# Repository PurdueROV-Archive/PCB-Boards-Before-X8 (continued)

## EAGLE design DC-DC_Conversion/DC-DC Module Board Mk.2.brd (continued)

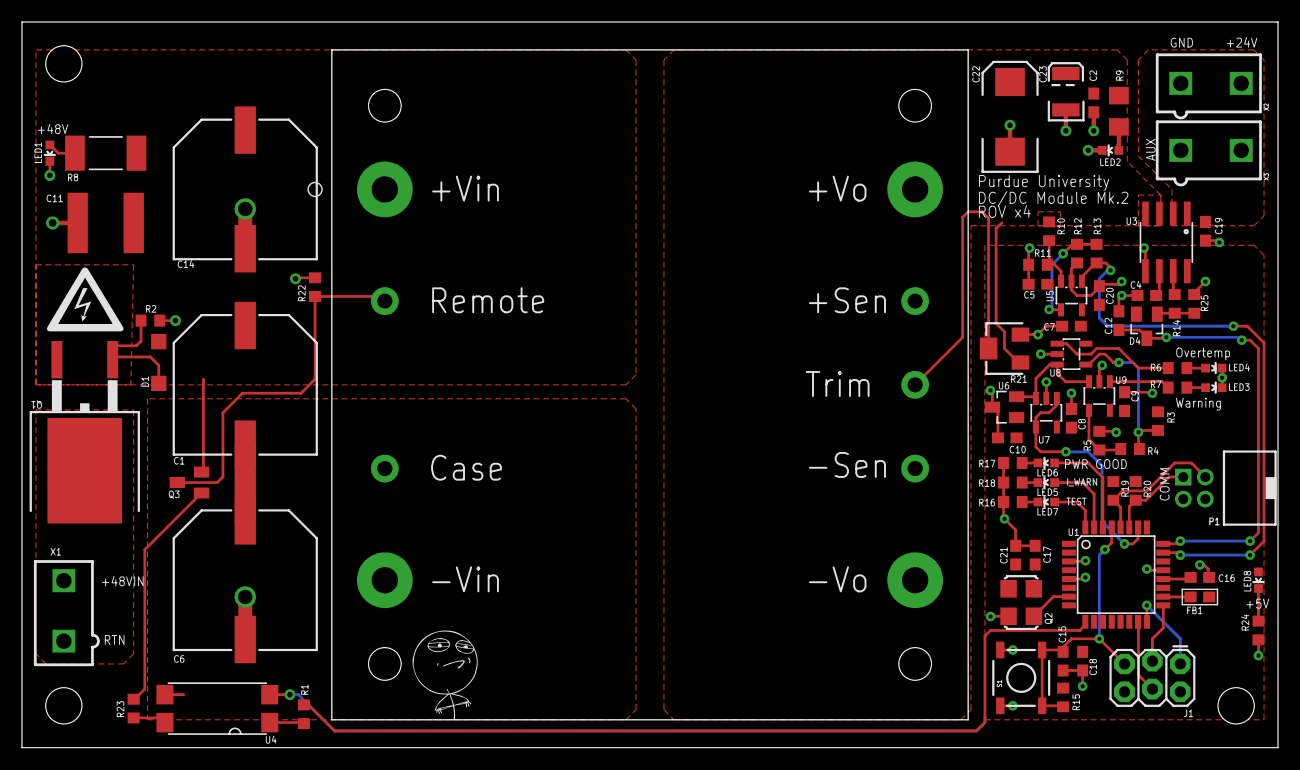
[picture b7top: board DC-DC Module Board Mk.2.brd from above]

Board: 2 copper layers, 114.3 x 66.0 mm, 78 parts (0 on the bottom side), 48 nets.

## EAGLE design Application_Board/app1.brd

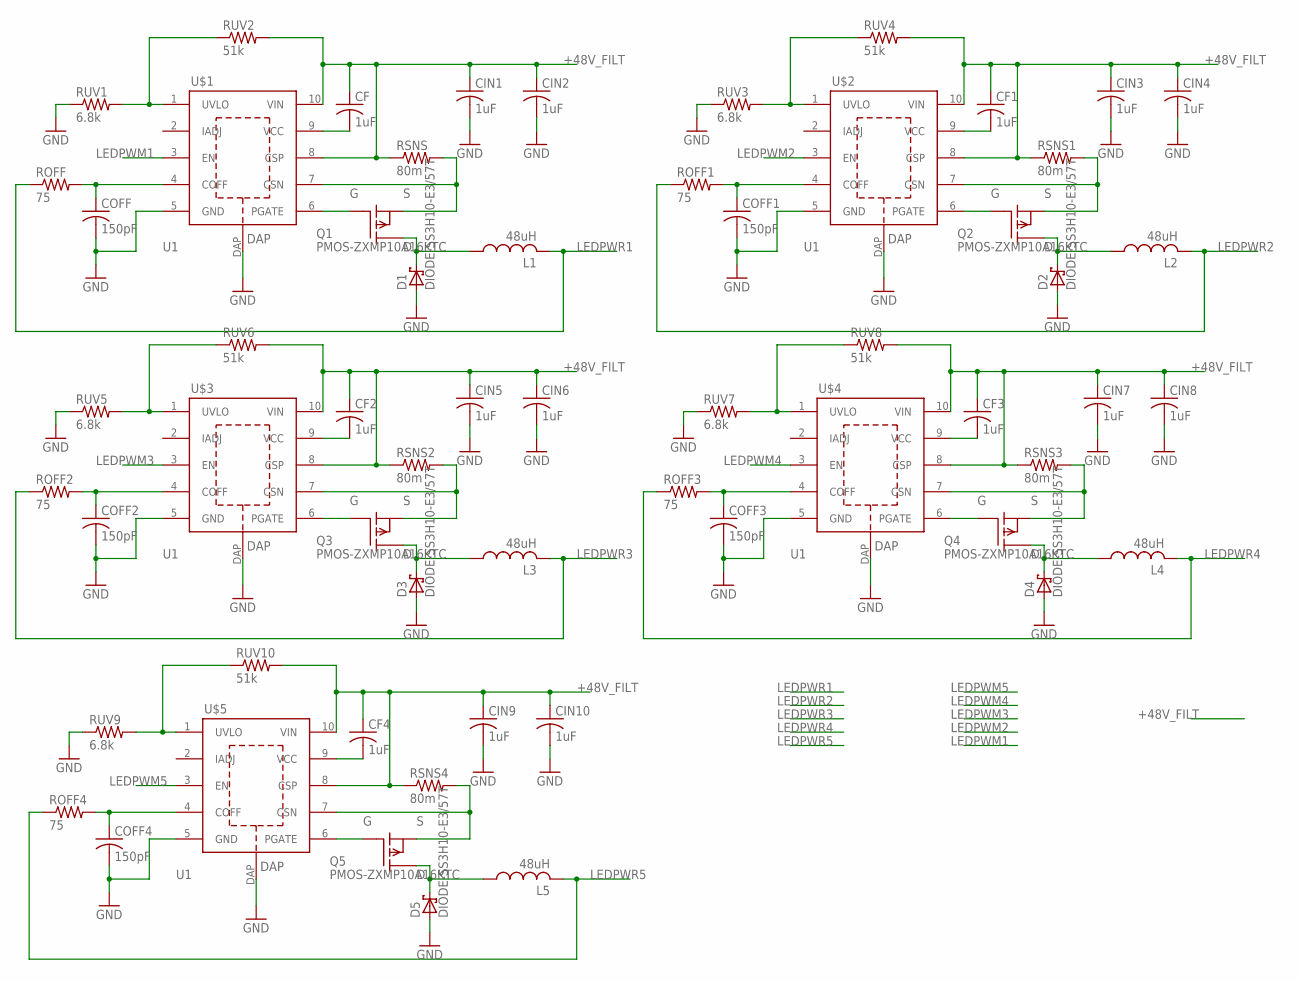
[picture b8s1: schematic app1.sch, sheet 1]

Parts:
CF, CF1, CF2, CF3, CF4: 1uF; C0603
CIN1, CIN2, CIN3, CIN4, CIN5, CIN6, CIN7, CIN8, CIN9, CIN10: 1uF; C1206
COFF, COFF1, COFF2, COFF3, COFF4: 150pF; C0603
D1, D2, D3, D4, D5: DIODE-SS3H10-E3/57T; SMC
L1, L2, L3, L4, L5: 48uH; SRP1265A
Q1, Q2, Q3, Q4, Q5: PMOS-ZXMP10A16KTC; TO252
ROFF, ROFF1, ROFF2, ROFF3, ROFF4: 75; R0603
RSNS, RSNS1, RSNS2, RSNS3, RSNS4: 80m; R2512
RUV1, RUV3, RUV5, RUV7, RUV9: 6.8k; R0603
RUV2, RUV4, RUV6, RUV8, RUV10: 51k; R0603
U$1, U$2, U$3, U$4, U$5: U1; VSSOP-10

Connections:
+48V_FILT: CF.1, CF1.1, CF2.1, CF3.1, CF4.1, CIN1.1, CIN2.1, CIN3.1, CIN4.1, CIN5.1, CIN6.1, CIN7.1, CIN8.1, CIN9.1, CIN10.1, RSNS.1, RSNS1.1, RSNS2.1, RSNS3.1, RSNS4.1, RUV2.2, RUV4.2, RUV6.2, RUV8.2, RUV10.2, U$1.8 (CSP), U$1.10 (VIN), U$2.8 (CSP), U$2.10 (VIN), U$3.8 (CSP), U$3.10 (VIN), U$4.8 (CSP), U$4.10 (VIN), U$5.8 (CSP), U$5.10 (VIN); also elsewhere on the board
GND: CIN1.2, CIN2.2, CIN3.2, CIN4.2, CIN5.2, CIN6.2, CIN7.2, CIN8.2, CIN9.2, CIN10.2, COFF.2, COFF1.2, COFF2.2, COFF3.2, COFF4.2, D1.A, D2.A, D3.A, D4.A, D5.A, RUV1.1, RUV3.1, RUV5.1, RUV7.1, RUV9.1, U$1.5 (GND), U$1.DAP, U$2.5 (GND), U$2.DAP, U$3.5 (GND), U$3.DAP, U$4.5 (GND), U$4.DAP, U$5.5 (GND), U$5.DAP; also elsewhere on the board
LEDPWM1: U$1.3 (EN); also elsewhere on the board
LEDPWM2: U$2.3 (EN); also elsewhere on the board
LEDPWM3: U$3.3 (EN); also elsewhere on the board
LEDPWM4: U$4.3 (EN); also elsewhere on the board
LEDPWM5: U$5.3 (EN); also elsewhere on the board
LEDPWR1: L1.P$2 (2), ROFF.1; also elsewhere on the board
LEDPWR2: L2.P$2 (2), ROFF1.1; also elsewhere on the board
LEDPWR3: L3.P$2 (2), ROFF2.1; also elsewhere on the board
LEDPWR4: L4.P$2 (2), ROFF3.1; also elsewhere on the board
LEDPWR5: L5.P$2 (2), ROFF4.1; also elsewhere on the board
unnamed: RUV3.2, RUV4.1, U$2.1 (UVLO)
unnamed: RUV1.2, RUV2.1, U$1.1 (UVLO)
unnamed: CF.2, U$1.9 (VCC)
unnamed: Q1.2 (S), RSNS.2, U$1.7 (CSN)
unnamed: COFF.1, ROFF.2, U$1.4 (COFF)
unnamed: Q1.1 (G), U$1.6 (PGATE)
unnamed: D1.C, L1.P$1 (1), Q1.3 (D)
unnamed: CF1.2, U$2.9 (VCC)
unnamed: Q2.2 (S), RSNS1.2, U$2.7 (CSN)
unnamed: COFF1.1, ROFF1.2, U$2.4 (COFF)
unnamed: Q2.1 (G), U$2.6 (PGATE)
unnamed: D2.C, L2.P$1 (1), Q2.3 (D)
unnamed: RUV5.2, RUV6.1, U$3.1 (UVLO)
unnamed: CF2.2, U$3.9 (VCC)
unnamed: Q3.2 (S), RSNS2.2, U$3.7 (CSN)
unnamed: COFF2.1, ROFF2.2, U$3.4 (COFF)
unnamed: Q3.1 (G), U$3.6 (PGATE)
unnamed: D3.C, L3.P$1 (1), Q3.3 (D)
unnamed: RUV7.2, RUV8.1, U$4.1 (UVLO)
unnamed: CF3.2, U$4.9 (VCC)
unnamed: Q4.2 (S), RSNS3.2, U$4.7 (CSN)
unnamed: COFF3.1, ROFF3.2, U$4.4 (COFF)
unnamed: Q4.1 (G), U$4.6 (PGATE)
unnamed: D4.C, L4.P$1 (1), Q4.3 (D)
unnamed: RUV9.2, RUV10.1, U$5.1 (UVLO)
unnamed: CF4.2, U$5.9 (VCC)
unnamed: Q5.2 (S), RSNS4.2, U$5.7 (CSN)
unnamed: COFF4.1, ROFF4.2, U$5.4 (COFF)
unnamed: Q5.1 (G), U$5.6 (PGATE)
unnamed: D5.C, L5.P$1 (1), Q5.3 (D)

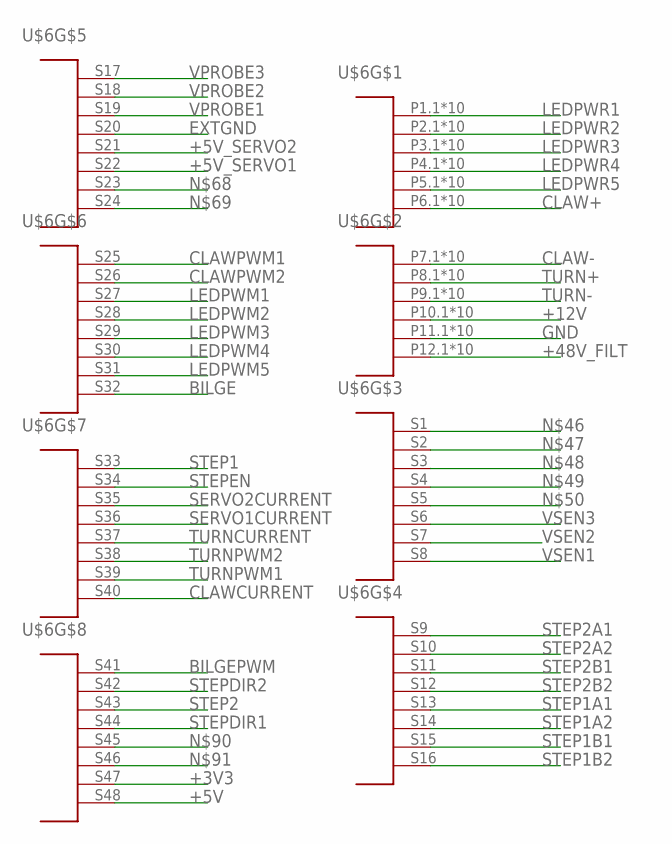
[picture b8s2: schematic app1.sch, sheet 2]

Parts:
U$6: TEN60-P6-S24-S24-P6-RA

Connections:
+3V3: U$6.S47; also elsewhere on the board
+5V: U$6.S48; also elsewhere on the board
+5V_SERVO1: U$6.S22; also elsewhere on the board
+5V_SERVO2: U$6.S21; also elsewhere on the board
+12V: U$6.P10.1, U$6.P10.2, U$6.P10.3, U$6.P10.4, U$6.P10.5, U$6.P10.6, U$6.P10.7, U$6.P10.8, U$6.P10.9, U$6.P10.10; also elsewhere on the board
+48V_FILT: U$6.P12.1, U$6.P12.2, U$6.P12.3, U$6.P12.4, U$6.P12.5, U$6.P12.6, U$6.P12.7, U$6.P12.8, U$6.P12.9, U$6.P12.10; also elsewhere on the board
BILGE: U$6.S32; also elsewhere on the board
BILGEPWM: U$6.S41; also elsewhere on the board
CLAW+: U$6.P6.1, U$6.P6.2, U$6.P6.3, U$6.P6.4, U$6.P6.5, U$6.P6.6, U$6.P6.7, U$6.P6.8, U$6.P6.9, U$6.P6.10; also elsewhere on the board
CLAW-: U$6.P7.1, U$6.P7.2, U$6.P7.3, U$6.P7.4, U$6.P7.5, U$6.P7.6, U$6.P7.7, U$6.P7.8, U$6.P7.9, U$6.P7.10; also elsewhere on the board
CLAWCURRENT: U$6.S40; also elsewhere on the board
CLAWPWM1: U$6.S25; also elsewhere on the board
CLAWPWM2: U$6.S26; also elsewhere on the board
EXTGND: U$6.S20; also elsewhere on the board
GND: U$6.P11.1, U$6.P11.2, U$6.P11.3, U$6.P11.4, U$6.P11.5, U$6.P11.6, U$6.P11.7, U$6.P11.8, U$6.P11.9, U$6.P11.10; also elsewhere on the board
LEDPWM1: U$6.S27; also elsewhere on the board
LEDPWM2: U$6.S28; also elsewhere on the board
LEDPWM3: U$6.S29; also elsewhere on the board
LEDPWM4: U$6.S30; also elsewhere on the board
LEDPWM5: U$6.S31; also elsewhere on the board
LEDPWR1: U$6.P1.1, U$6.P1.2, U$6.P1.3, U$6.P1.4, U$6.P1.5, U$6.P1.6, U$6.P1.7, U$6.P1.8, U$6.P1.9, U$6.P1.10; also elsewhere on the board
LEDPWR2: U$6.P2.1, U$6.P2.2, U$6.P2.3, U$6.P2.4, U$6.P2.5, U$6.P2.6, U$6.P2.7, U$6.P2.8, U$6.P2.9, U$6.P2.10; also elsewhere on the board
LEDPWR3: U$6.P3.1, U$6.P3.2, U$6.P3.3, U$6.P3.4, U$6.P3.5, U$6.P3.6, U$6.P3.7, U$6.P3.8, U$6.P3.9, U$6.P3.10; also elsewhere on the board
LEDPWR4: U$6.P4.1, U$6.P4.2, U$6.P4.3, U$6.P4.4, U$6.P4.5, U$6.P4.6, U$6.P4.7, U$6.P4.8, U$6.P4.9, U$6.P4.10; also elsewhere on the board
LEDPWR5: U$6.P5.1, U$6.P5.2, U$6.P5.3, U$6.P5.4, U$6.P5.5, U$6.P5.6, U$6.P5.7, U$6.P5.8, U$6.P5.9, U$6.P5.10; also elsewhere on the board
SERVO1CURRENT: U$6.S36; also elsewhere on the board
SERVO2CURRENT: U$6.S35; also elsewhere on the board
STEP1: U$6.S33; also elsewhere on the board
STEP1A1: U$6.S13; also elsewhere on the board
STEP1A2: U$6.S14; also elsewhere on the board
STEP1B1: U$6.S15; also elsewhere on the board
STEP1B2: U$6.S16; also elsewhere on the board
STEP2: U$6.S43; also elsewhere on the board
STEP2A1: U$6.S9; also elsewhere on the board
STEP2A2: U$6.S10; also elsewhere on the board
STEP2B1: U$6.S11; also elsewhere on the board
STEP2B2: U$6.S12; also elsewhere on the board
STEPDIR1: U$6.S44; also elsewhere on the board
STEPDIR2: U$6.S42; also elsewhere on the board
STEPEN: U$6.S34; also elsewhere on the board
TURN+: U$6.P8.1, U$6.P8.2, U$6.P8.3, U$6.P8.4, U$6.P8.5, U$6.P8.6, U$6.P8.7, U$6.P8.8, U$6.P8.9, U$6.P8.10; also elsewhere on the board
TURN-: U$6.P9.1, U$6.P9.2, U$6.P9.3, U$6.P9.4, U$6.P9.5, U$6.P9.6, U$6.P9.7, U$6.P9.8, U$6.P9.9, U$6.P9.10; also elsewhere on the board
TURNCURRENT: U$6.S37; also elsewhere on the board
TURNPWM1: U$6.S39; also elsewhere on the board
TURNPWM2: U$6.S38; also elsewhere on the board
VPROBE1: U$6.S19; also elsewhere on the board
VPROBE2: U$6.S18; also elsewhere on the board
VPROBE3: U$6.S17; also elsewhere on the board
VSEN1: U$6.S8; also elsewhere on the board
VSEN2: U$6.S7; also elsewhere on the board
VSEN3: U$6.S6; also elsewhere on the board

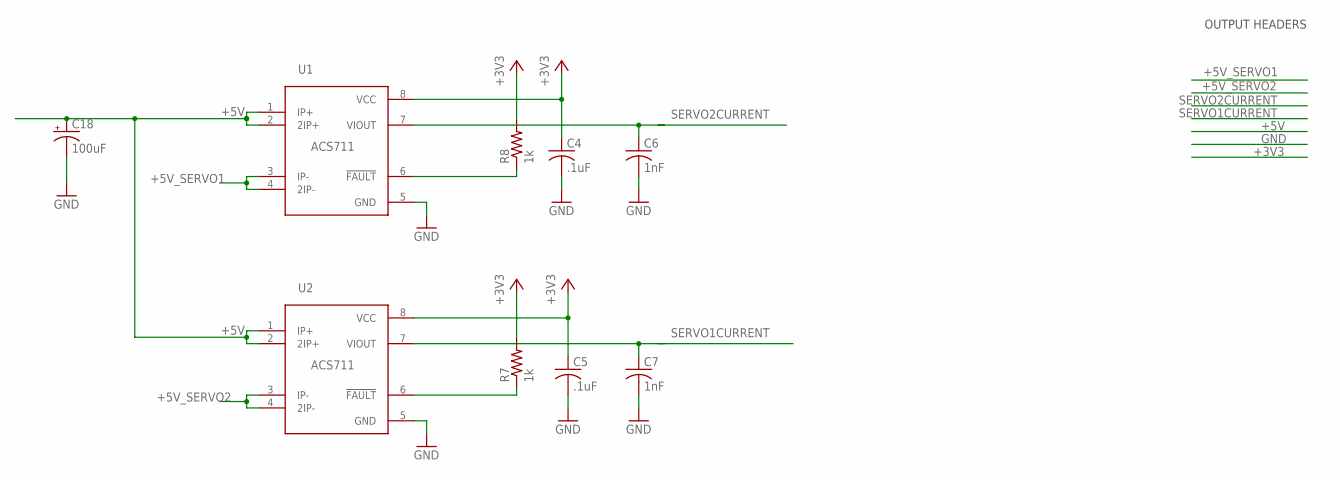
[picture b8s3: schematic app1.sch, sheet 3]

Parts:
C4, C5: .1uF; C0603
C6, C7: 1nF; C0603K
C18: 100uF; SANYO-OSCON_SMD_B6
R7, R8: 1k; R0603
U1, U2: ACS711; 8SOIC

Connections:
+3V3: C4.1, C5.1, R7.2, R8.2, U1.8 (VCC), U2.8 (VCC); also elsewhere on the board
+5V: C18.+, U1.1 (IP+), U1.2 (2IP+), U2.1 (IP+), U2.2 (2IP+); also elsewhere on the board
+5V_SERVO1: U1.3 (IP-), U1.4 (2IP-); also elsewhere on the board
+5V_SERVO2: U2.3 (IP-), U2.4 (2IP-); also elsewhere on the board
GND: C4.2, C5.2, C6.2, C7.2, C18.-, U1.5 (GND), U2.5 (GND); also elsewhere on the board
unnamed: R7.1, U2.6 (!FAULT)
unnamed: R8.1, U1.6 (!FAULT)
SERVO1CURRENT: C7.1, U2.7 (VIOUT); also elsewhere on the board
SERVO2CURRENT: C6.1, U1.7 (VIOUT); also elsewhere on the board

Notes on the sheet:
OUTPUT HEADERS

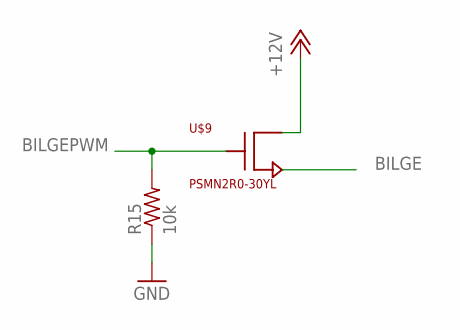
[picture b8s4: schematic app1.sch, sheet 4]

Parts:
R15: 10k; R0603
U$9: PSMN2R0-30YL; SOT669

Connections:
+12V: U$9.MB (DRAIN); also elsewhere on the board
BILGE: U$9.1 (SOURCE), U$9.2 (SOURCE), U$9.3 (SOURCE); also elsewhere on the board
BILGEPWM: R15.2, U$9.4 (GATE); also elsewhere on the board
GND: R15.1; also elsewhere on the board

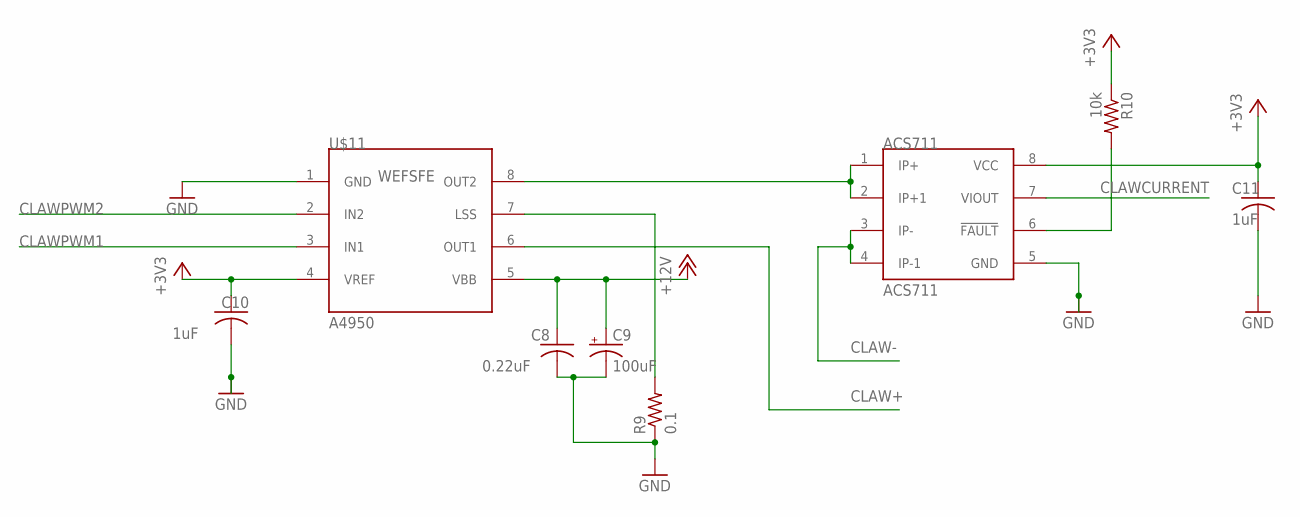
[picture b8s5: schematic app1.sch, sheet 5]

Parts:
ACS711: ACS711; SOIC8
C8: 0.22uF; C0603
C9: 100uF; SANYO-OSCON_SMD_B6
C10, C11: 1uF; C0603
R9: 0.1; R0603
R10: 10k; R0603
U$11: A4950; SOIC8-PAD

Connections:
+3V3: ACS711.8 (VCC), C10.1, C11.1, R10.1, U$11.4 (VREF); also elsewhere on the board
+12V: C8.1, C9.+, U$11.5 (VBB); also elsewhere on the board
CLAW+: U$11.6 (OUT1); also elsewhere on the board
CLAW-: ACS711.3 (IP-), ACS711.4 (IP-1); also elsewhere on the board
CLAWCURRENT: ACS711.7 (VIOUT); also elsewhere on the board
CLAWPWM1: U$11.3 (IN1); also elsewhere on the board
CLAWPWM2: U$11.2 (IN2); also elsewhere on the board
GND: ACS711.5 (GND), C8.2, C9.-, C10.2, C11.2, R9.1, U$11.1 (GND); also elsewhere on the board
unnamed: R9.2, U$11.7 (LSS)
unnamed: ACS711.6 (!FAULT), R10.2
WEFSFE: ACS711.1 (IP+), ACS711.2 (IP+1), U$11.8 (OUT2)

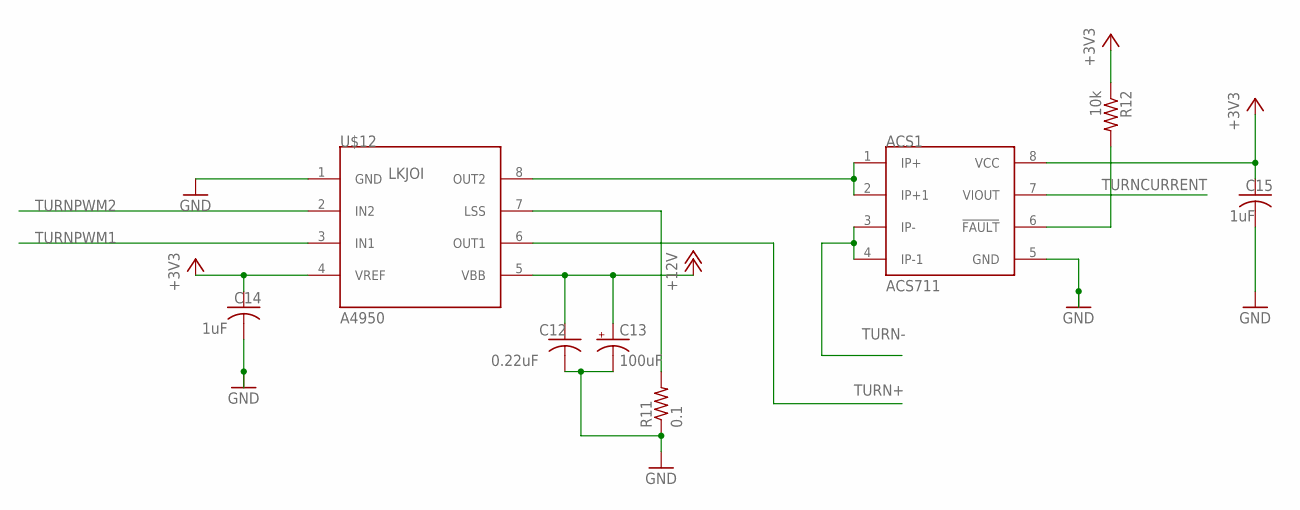
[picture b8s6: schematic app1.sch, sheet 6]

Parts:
ACS1: ACS711; SOIC8
C12: 0.22uF; C0603
C13: 100uF; SANYO-OSCON_SMD_B6
C14, C15: 1uF; C0603
R11: 0.1; R0603
R12: 10k; R0603
U$12: A4950; SOIC8-PAD

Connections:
+3V3: ACS1.8 (VCC), C14.1, C15.1, R12.1, U$12.4 (VREF); also elsewhere on the board
+12V: C12.1, C13.+, U$12.5 (VBB); also elsewhere on the board
GND: ACS1.5 (GND), C12.2, C13.-, C14.2, C15.2, R11.1, U$12.1 (GND); also elsewhere on the board
LKJOI: ACS1.1 (IP+), ACS1.2 (IP+1), U$12.8 (OUT2)
unnamed: R11.2, U$12.7 (LSS)
unnamed: ACS1.6 (!FAULT), R12.2
TURN+: U$12.6 (OUT1); also elsewhere on the board
TURN-: ACS1.3 (IP-), ACS1.4 (IP-1); also elsewhere on the board
TURNCURRENT: ACS1.7 (VIOUT); also elsewhere on the board
TURNPWM1: U$12.3 (IN1); also elsewhere on the board
TURNPWM2: U$12.2 (IN2); also elsewhere on the board

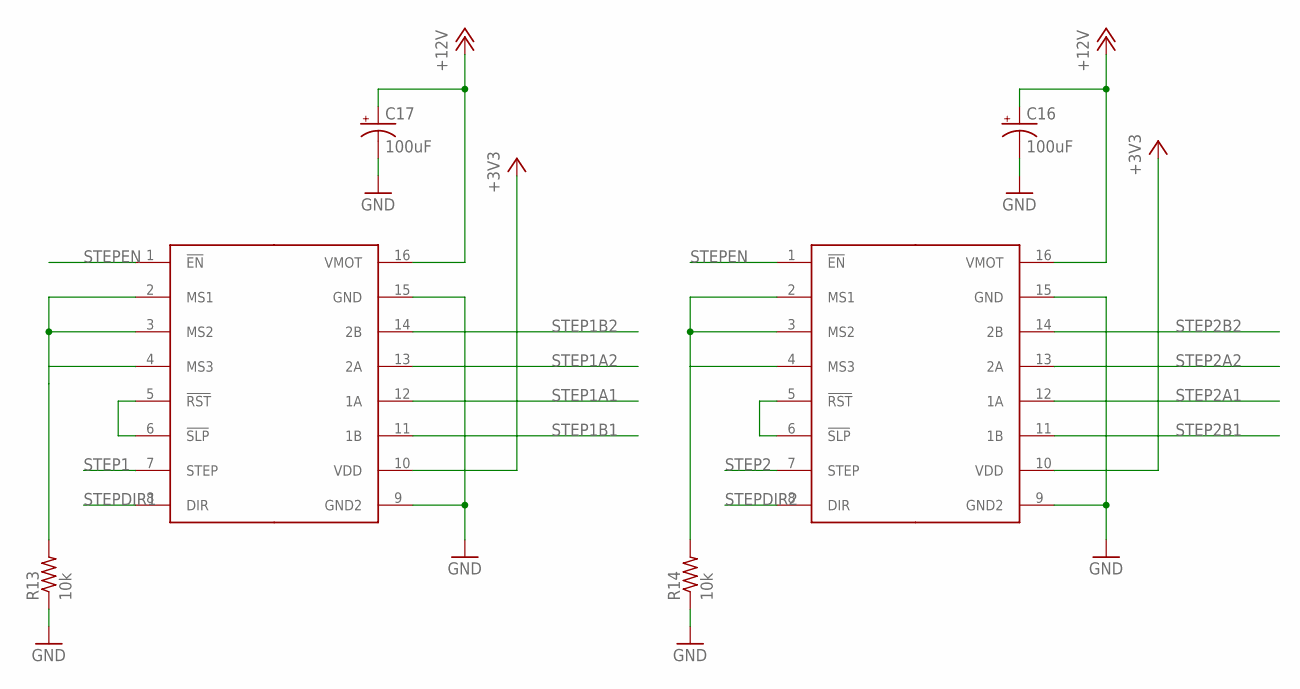
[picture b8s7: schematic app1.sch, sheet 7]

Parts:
C16, C17: 100uF; SANYO-OSCON_SMD_B6
R13, R14: 10k; R0603
U$7, U$8: A4988; FE08-2-0.6

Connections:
+3V3: U$7.10 (VDD), U$8.10 (VDD); also elsewhere on the board
+12V: C16.+, C17.+, U$7.16 (VMOT), U$8.16 (VMOT); also elsewhere on the board
GND: C16.-, C17.-, R13.1, R14.1, U$7.9 (GND2), U$7.15 (GND), U$8.9 (GND2), U$8.15 (GND); also elsewhere on the board
unnamed: R13.2, U$7.2 (MS1), U$7.3 (MS2), U$7.4 (MS3)
unnamed: U$7.5 (!RST), U$7.6 (!SLP)
unnamed: R14.2, U$8.2 (MS1), U$8.3 (MS2), U$8.4 (MS3)
unnamed: U$8.5 (!RST), U$8.6 (!SLP)
STEP1: U$7.7 (STEP); also elsewhere on the board
STEP1A1: U$7.12 (1A); also elsewhere on the board
STEP1A2: U$7.13 (2A); also elsewhere on the board
STEP1B1: U$7.11 (1B); also elsewhere on the board
STEP1B2: U$7.14 (2B); also elsewhere on the board
STEP2: U$8.7 (STEP); also elsewhere on the board
STEP2A1: U$8.12 (1A); also elsewhere on the board
STEP2A2: U$8.13 (2A); also elsewhere on the board
STEP2B1: U$8.11 (1B); also elsewhere on the board
STEP2B2: U$8.14 (2B); also elsewhere on the board
STEPDIR1: U$7.8 (DIR); also elsewhere on the board
STEPDIR2: U$8.8 (DIR); also elsewhere on the board
STEPEN: U$7.1 (!EN), U$8.1 (!EN); also elsewhere on the board

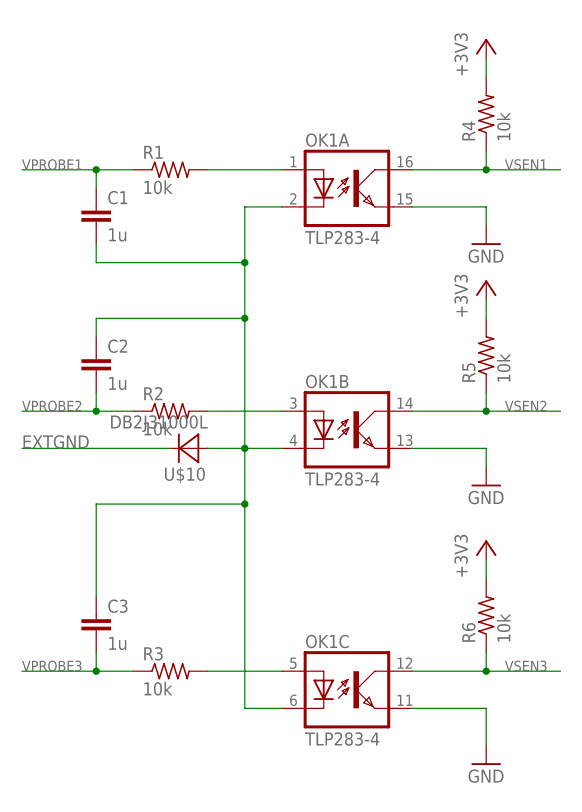
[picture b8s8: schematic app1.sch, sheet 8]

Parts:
C1, C2, C3: 1u; C0603
OK1: TLP283-4; MINI-FLAT-16
R1, R2, R3, R4, R5, R6: 10k; R0603
U$10: DB2J31000L; SOD323-R

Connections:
23989SDFJA: C1.2, C2.1, C3.1, OK1.2 (C), OK1.4 (C), OK1.6 (C), U$10.A
+3V3: R4.2, R5.2, R6.2; also elsewhere on the board
EXTGND: U$10.C; also elsewhere on the board
GND: OK1.11 (EMIT), OK1.13 (EMIT), OK1.15 (EMIT); also elsewhere on the board
unnamed: OK1.1 (A), R1.2
unnamed: OK1.3 (A), R2.2
unnamed: OK1.5 (A), R3.2
VPROBE1: C1.1, R1.1; also elsewhere on the board
VPROBE2: C2.2, R2.1; also elsewhere on the board
VPROBE3: C3.2, R3.1; also elsewhere on the board
VSEN1: OK1.16 (COL), R4.1; also elsewhere on the board
VSEN2: OK1.14 (COL), R5.1; also elsewhere on the board
VSEN3: OK1.12 (COL), R6.1; also elsewhere on the board

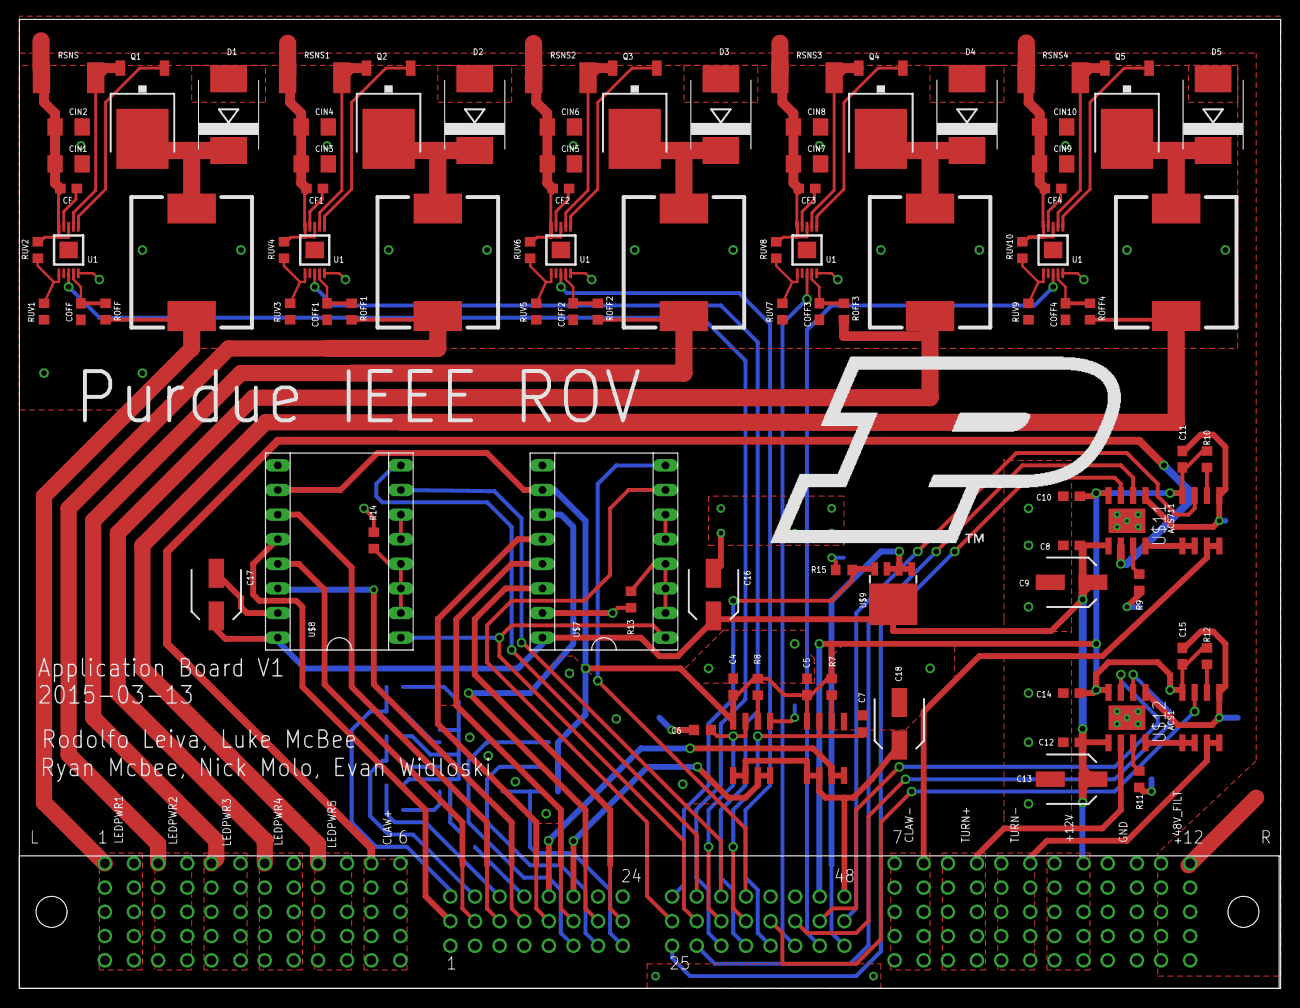
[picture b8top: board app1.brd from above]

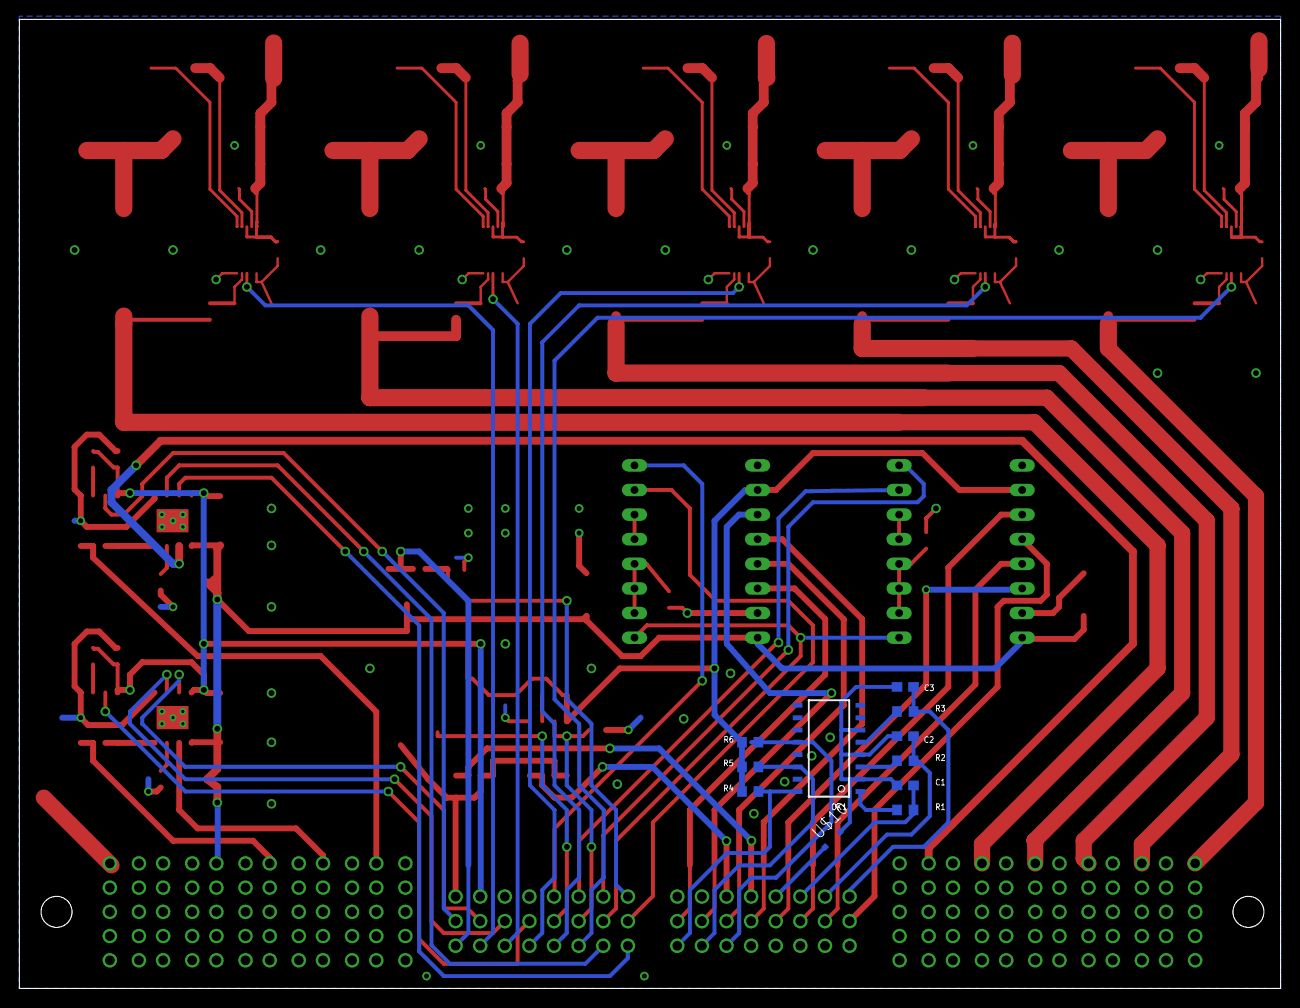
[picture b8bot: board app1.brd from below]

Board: 2 copper layers, 130.2 x 100.0 mm, 105 parts (11 on the bottom side), 97 nets.
